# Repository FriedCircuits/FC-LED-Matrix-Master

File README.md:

FC-LED-Matrix-Master
================

Info: <http://friedcircuits.us/docs/led-matrix/led-matrix-master/>

Purchase: <https://www.tindie.com/products/FriedCircuits/led-matrix-master/>

Folders:

Hardware - Design files

Code - Test code that comes pre-flashed. Allows testing of all LEDs on a 8x8 Matrix.

License: All source code and designs are released under 

Creative Commons NonCommercial-ShareAlike 

CC BY-NC-SA

Please contact me for commercial opportunities.

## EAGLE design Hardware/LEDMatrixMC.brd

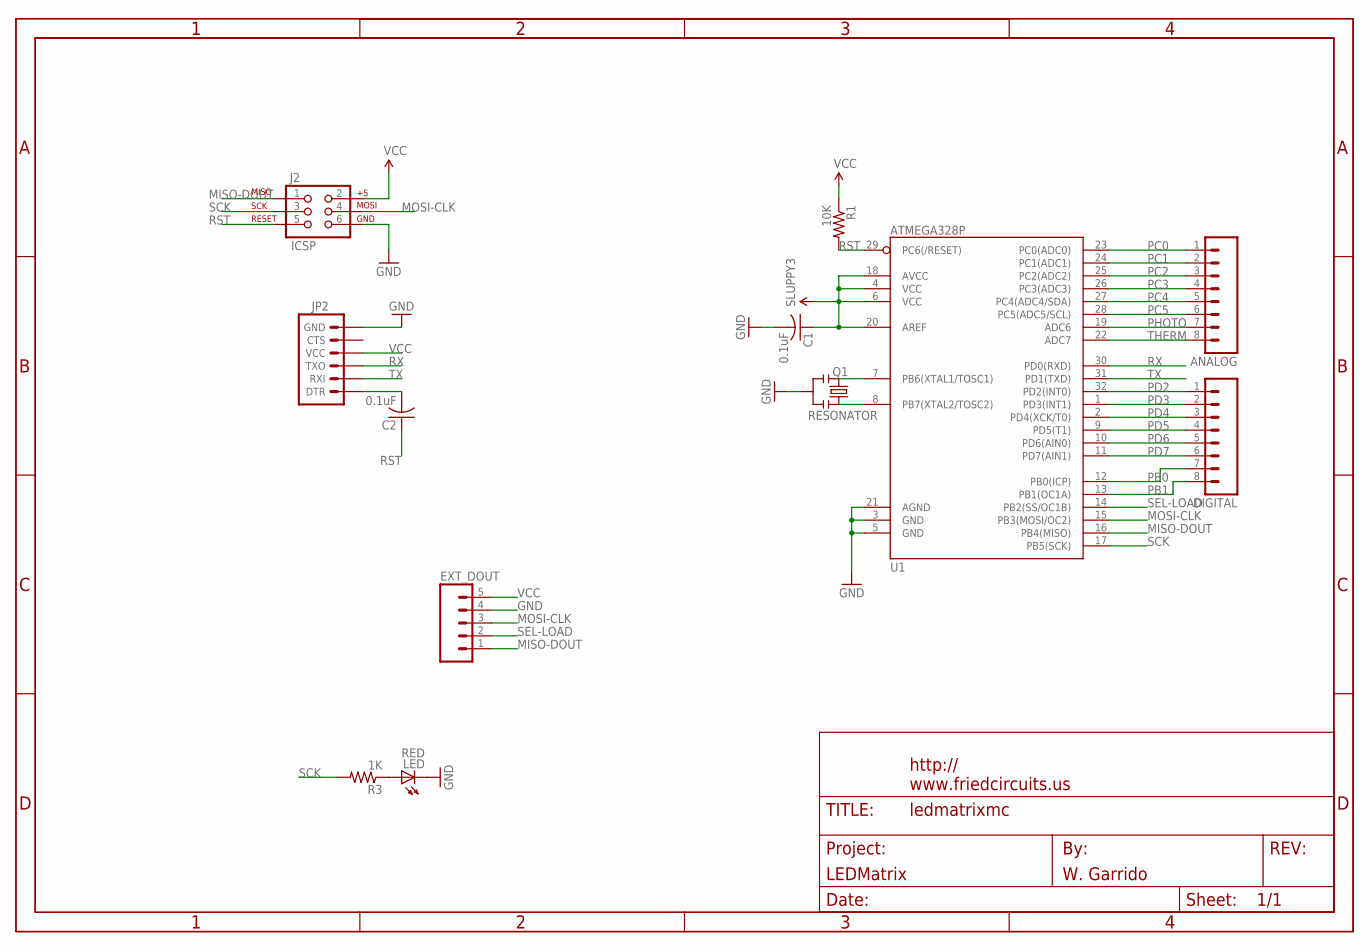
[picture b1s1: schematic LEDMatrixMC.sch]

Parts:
ANALOG: M08LOCK; 1X08_LOCK
C1, C2: 0.1uF; C0805K
DIGITAL: M08LOCK; 1X08_LOCK
EXT_DOUT: M05LOCK_LONGPADS; 1X05_LOCK_LONGPADS
J2: ICSP; 2X3_LOCK
JP2: ARDUINO_SERIAL_PROGRAMLOCK; 1X06_LOCK
LED: RED; CHIPLED_0805
Q1: RESONATOR; RESONATOR-SMD
R1: 10K; R0805
R3: 1K; R0805
U1: ATMEGA328P; TQFP32-08
U$1: FRAME_DINA4_L; FC_CREDIT

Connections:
GND: C1.2, EXT_DOUT.4, J2.6, JP2.6 (GND), LED.C, Q1.2, U1.3 (GND), U1.5 (GND), U1.21 (AGND)
MISO-DOUT: EXT_DOUT.1, J2.1, U1.16 (PB4(MISO))
MOSI-CLK: EXT_DOUT.3, J2.4, U1.15 (PB3(MOSI/OC2))
unnamed: C2.2, JP2.1 (DTR)
unnamed: Q1.1, U1.8 (PB7(XTAL2/TOSC2))
unnamed: Q1.3, U1.7 (PB6(XTAL1/TOSC1))
unnamed: LED.A, R3.1
PB0: DIGITAL.7, U1.12 (PB0(ICP))
PB1: DIGITAL.8, U1.13 (PB1(OC1A))
PC0: ANALOG.1, U1.23 (PC0(ADC0))
PC1: ANALOG.2, U1.24 (PC1(ADC1))
PC2: ANALOG.3, U1.25 (PC2(ADC2))
PC3: ANALOG.4, U1.26 (PC3(ADC3))
PC4: ANALOG.5, U1.27 (PC4(ADC4/SDA))
PC5: ANALOG.6, U1.28 (PC5(ADC5/SCL))
PD2: DIGITAL.1, U1.32 (PD2(INT0))
PD3: DIGITAL.2, U1.1 (PD3(INT1))
PD4: DIGITAL.3, U1.2 (PD4(XCK/T0))
PD5: DIGITAL.4, U1.9 (PD5(T1))
PD6: DIGITAL.5, U1.10 (PD6(AIN0))
PD7: DIGITAL.6, U1.11 (PD7(AIN1))
PHOTO: ANALOG.7, U1.19 (ADC6)
RST: C2.1, J2.5, R1.2, U1.29 (PC6(/RESET))
RX: JP2.3 (TXO), U1.30 (PD0(RXD))
SCK: J2.3, R3.2, U1.17 (PB5(SCK))
SEL-LOAD: EXT_DOUT.2, U1.14 (PB2(SS/OC1B))
THERM: ANALOG.8, U1.22 (ADC7)
TX: JP2.2 (RXI), U1.31 (PD1(TXD))
VCC: C1.1, EXT_DOUT.5, J2.2, JP2.4 (VCC), R1.1, U1.4 (VCC), U1.6 (VCC), U1.18 (AVCC), U1.20 (AREF)

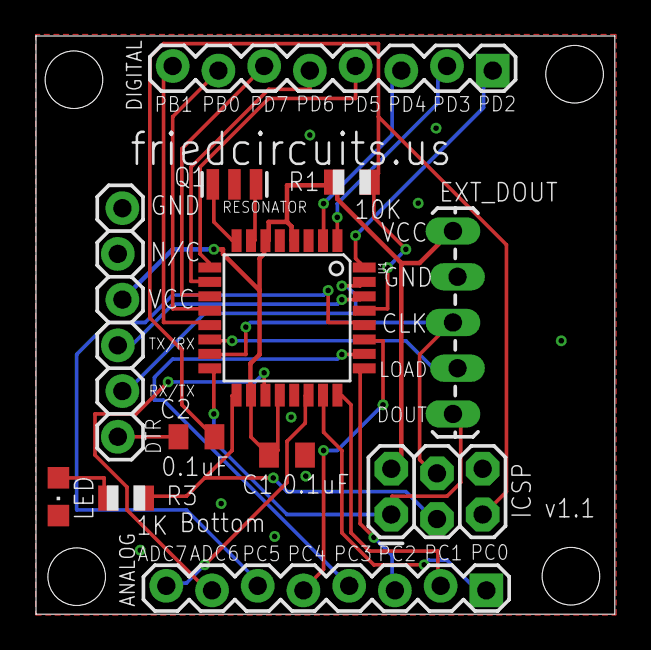
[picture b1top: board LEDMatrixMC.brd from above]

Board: 2 copper layers, 32.2 x 32.1 mm, 13 parts (0 on the bottom side), 29 nets.

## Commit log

2013-07-06 Added design and code files.

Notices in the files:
parts and their libraries:
SparkFun-Connectors: Licensing: CC v3.0 Share-Alike You are welcome to use this library for commercial purposes.
